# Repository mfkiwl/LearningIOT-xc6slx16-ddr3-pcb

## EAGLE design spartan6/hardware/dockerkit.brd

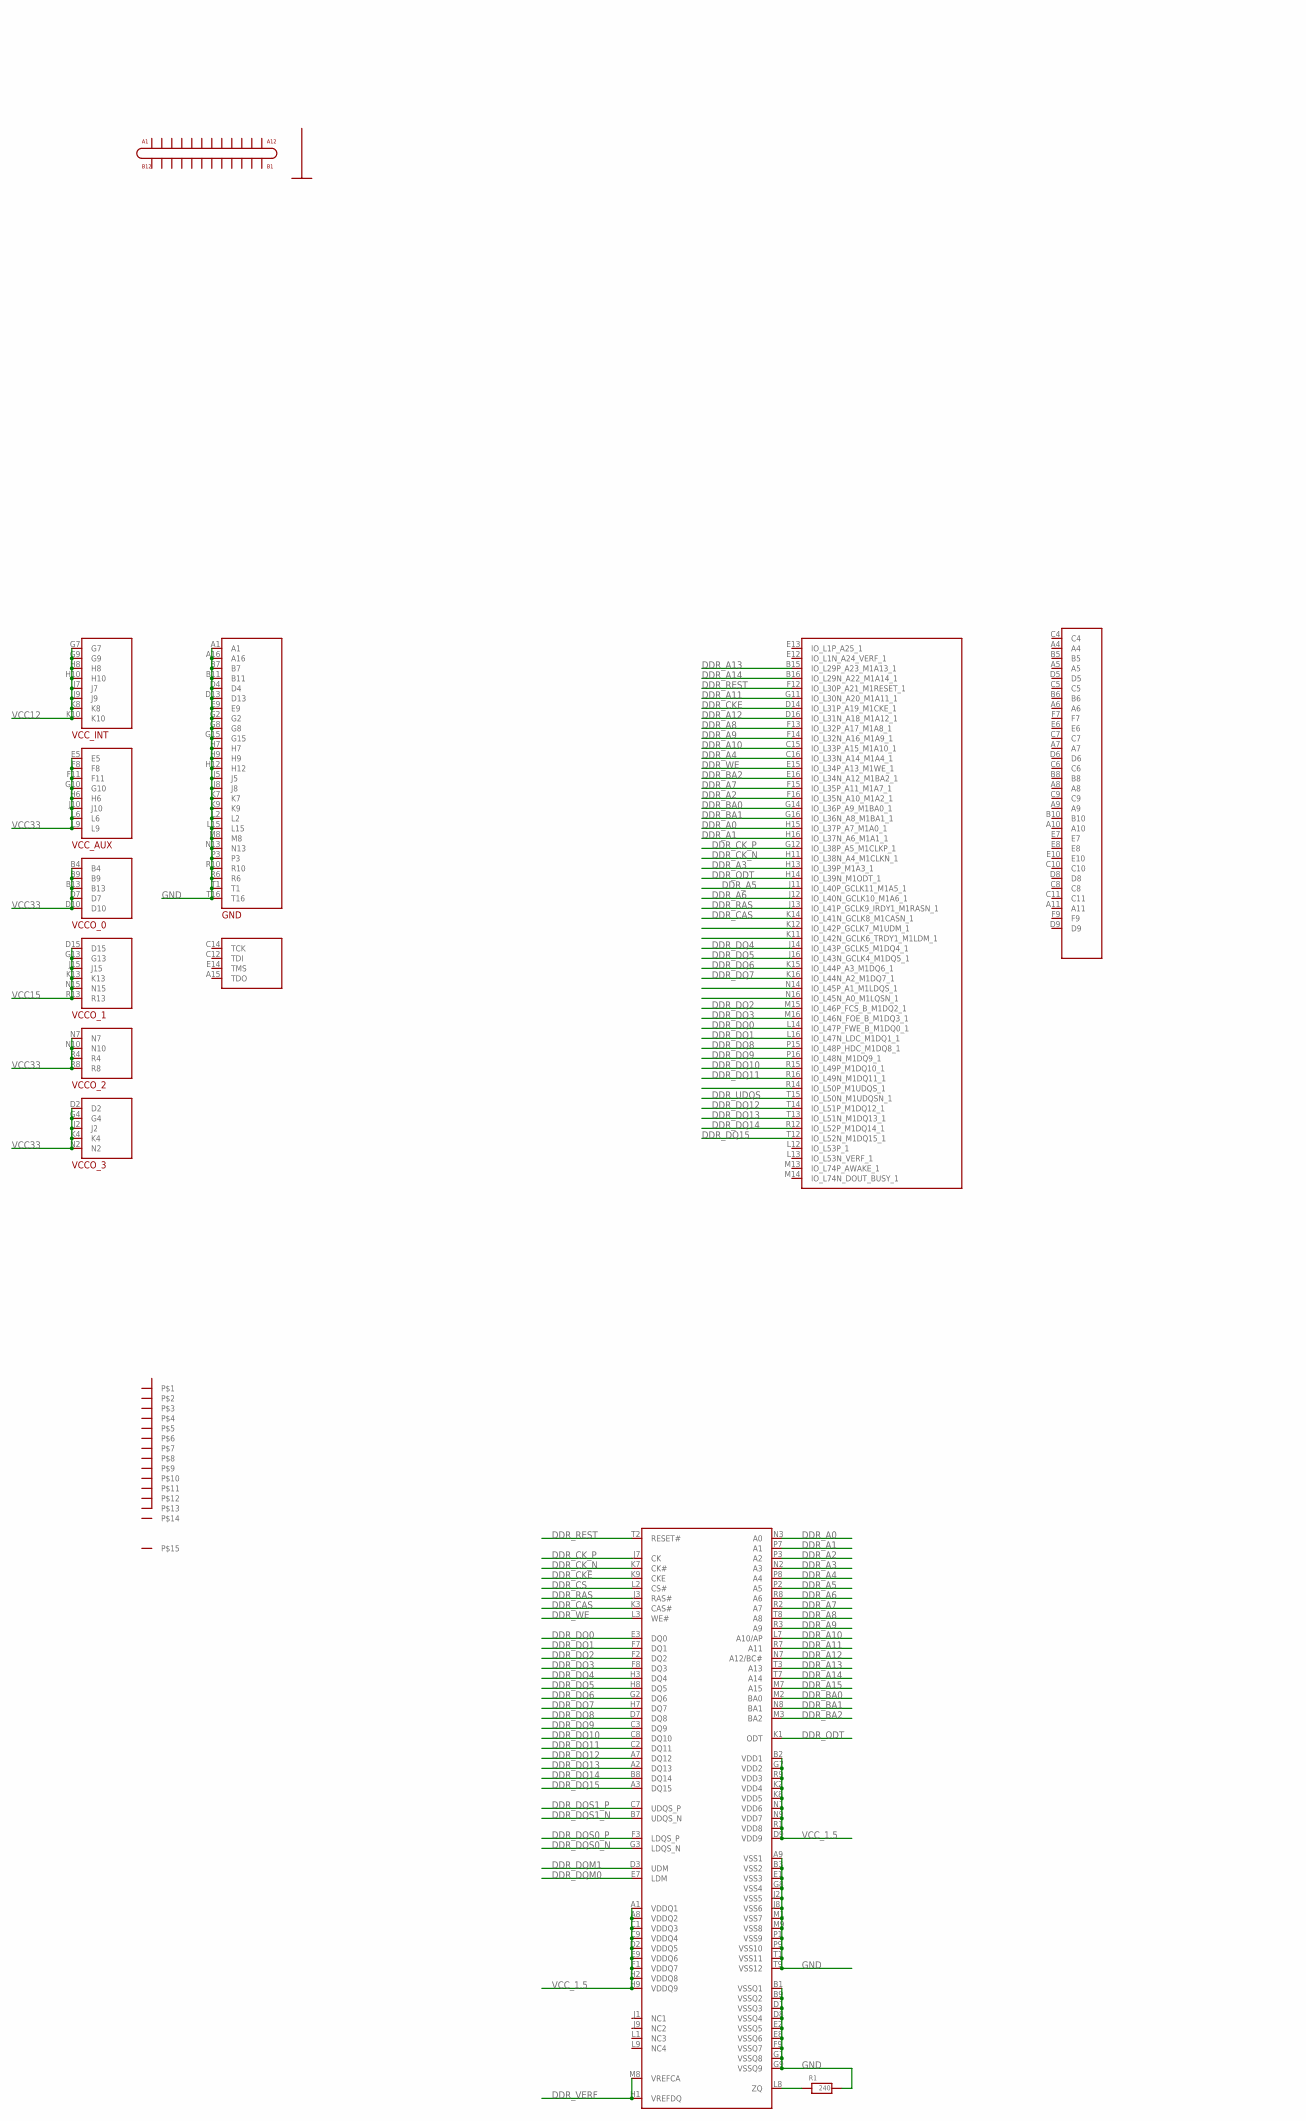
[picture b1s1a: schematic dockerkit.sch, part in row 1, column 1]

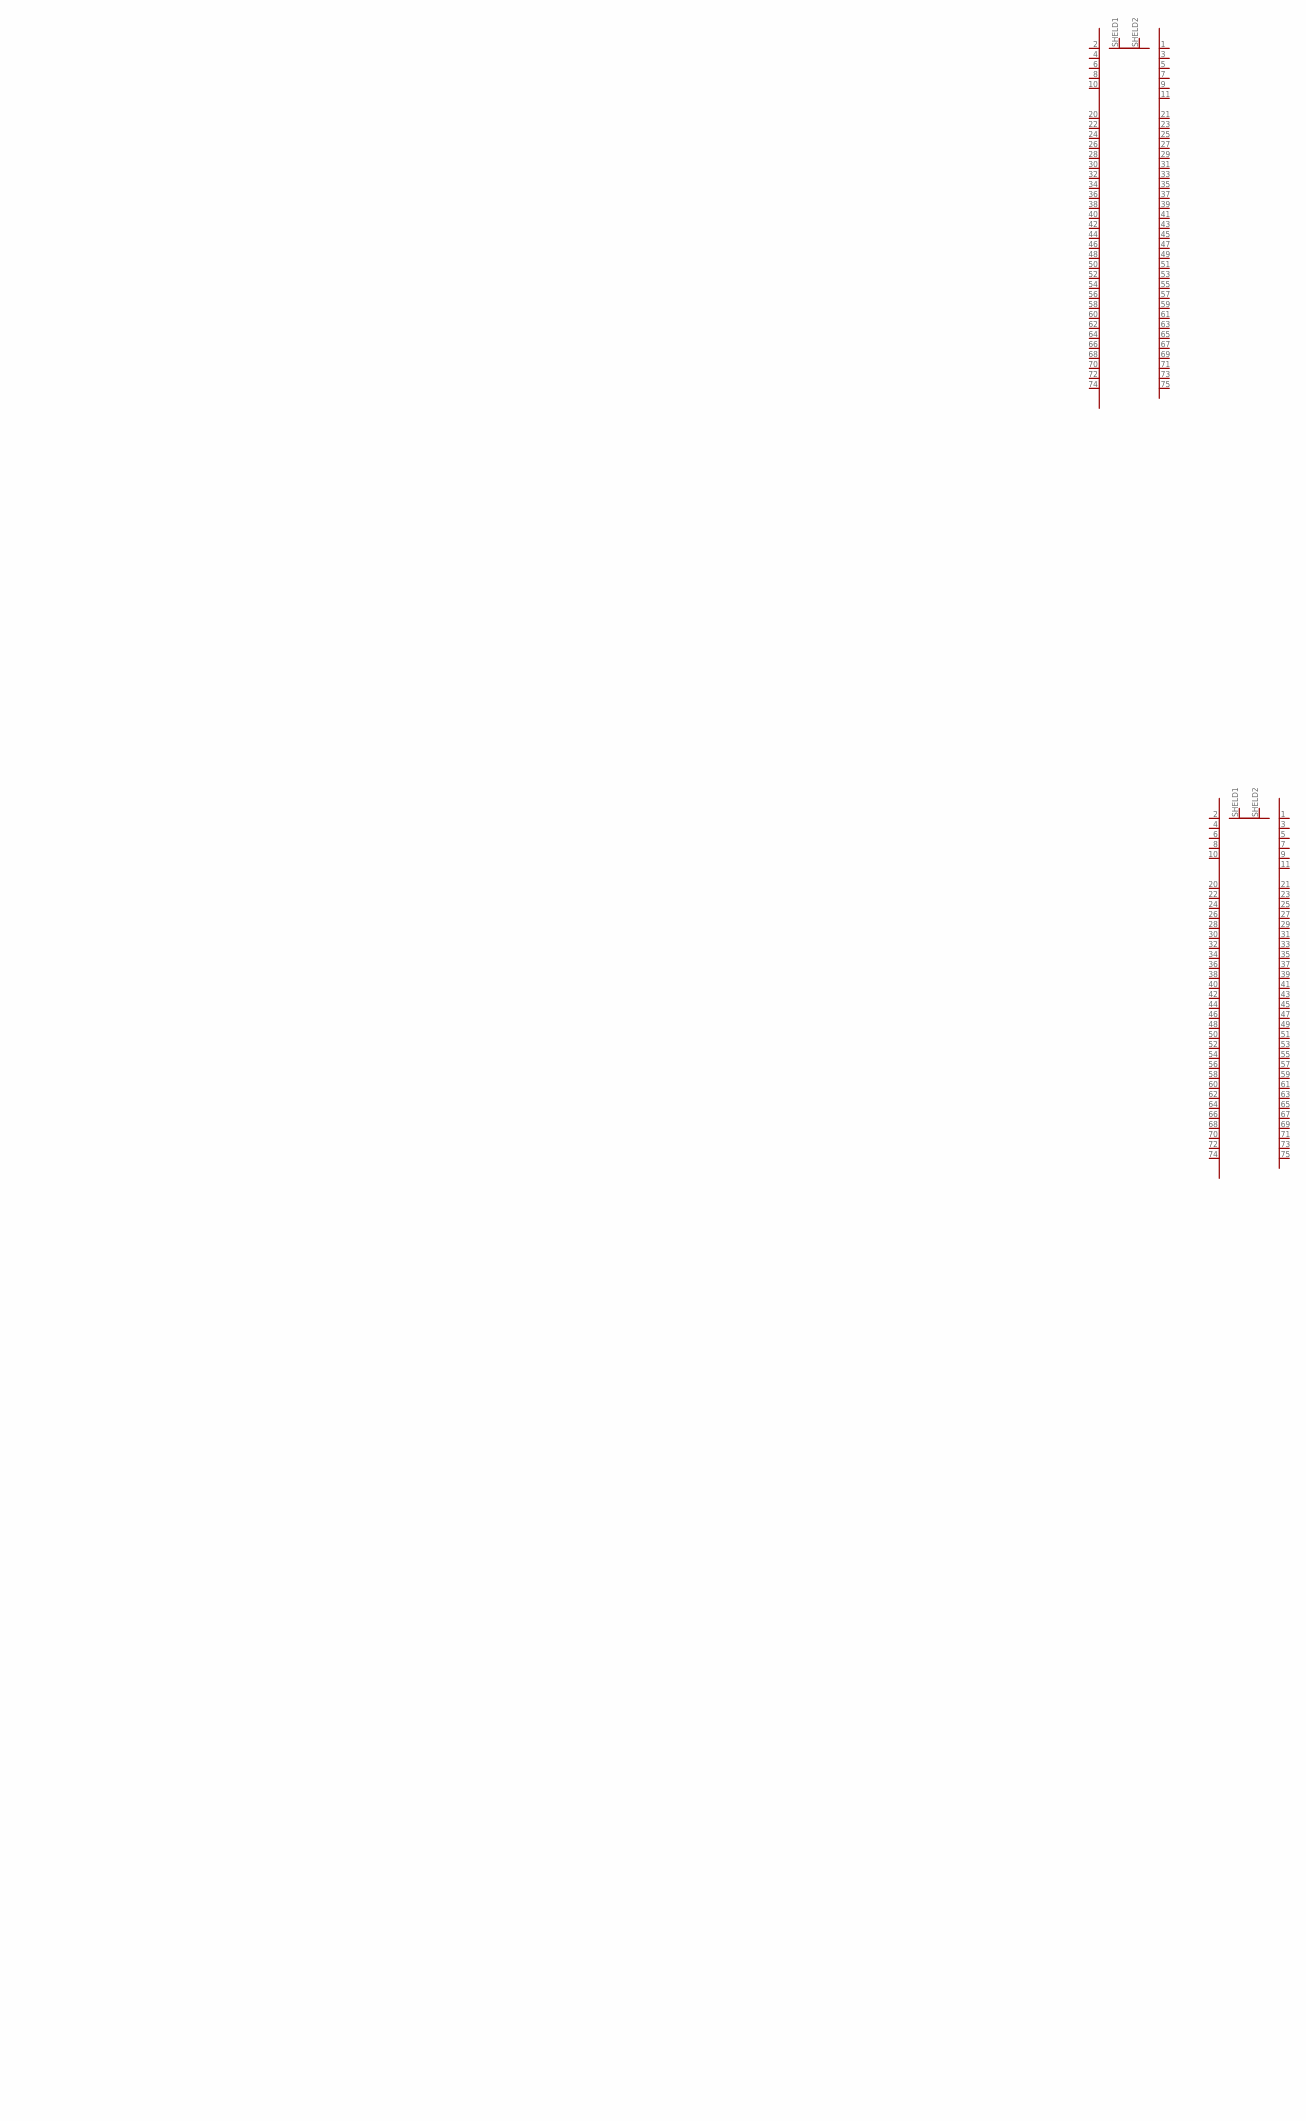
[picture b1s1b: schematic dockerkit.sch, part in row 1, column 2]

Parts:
R1: 240; R0402
U$1, U$3: B_KEY; NGFF_SOCKET
U$2: DDR3; FBGA96
U$4: XC6SLX16; FTG256
U$5: USB3.1; USB3.1_24PIN
U$8: GIGABYTE_14P; GIGABYTE_RJ45

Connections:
DDR_A0: U$2.N3 (A0), U$4.H15 (IO_L37P_A7_M1A0_1)
DDR_A1: U$2.P7 (A1), U$4.H16 (IO_L37N_A6_M1A1_1)
DDR_A2: U$2.P3 (A2), U$4.F16 (IO_L35N_A10_M1A2_1)
DDR_A3: U$2.N2 (A3), U$4.H13 (IO_L39P_M1A3_1)
DDR_A4: U$2.P8 (A4), U$4.C16 (IO_L33N_A14_M1A4_1)
DDR_A5: U$2.P2 (A5), U$4.J11 (IO_L40P_GCLK11_M1A5_1)
DDR_A6: U$2.R8 (A6), U$4.J12 (IO_L40N_GCLK10_M1A6_1)
DDR_A7: U$2.R2 (A7), U$4.F15 (IO_L35P_A11_M1A7_1)
DDR_A8: U$2.T8 (A8), U$4.F13 (IO_L32P_A17_M1A8_1)
DDR_A9: U$2.R3 (A9), U$4.F14 (IO_L32N_A16_M1A9_1)
DDR_A10: U$2.L7 (A10/AP), U$4.C15 (IO_L33P_A15_M1A10_1)
DDR_A11: U$2.R7 (A11), U$4.G11 (IO_L30N_A20_M1A11_1)
DDR_A12: U$2.N7 (A12/BC#), U$4.D16 (IO_L31N_A18_M1A12_1)
DDR_A13: U$2.T3 (A13), U$4.B15 (IO_L29P_A23_M1A13_1)
DDR_A14: U$2.T7 (A14), U$4.B16 (IO_L29N_A22_M1A14_1)
DDR_A15: U$2.M7 (A15)
DDR_BA0: U$2.M2 (BA0), U$4.G14 (IO_L36P_A9_M1BA0_1)
DDR_BA1: U$2.N8 (BA1), U$4.G16 (IO_L36N_A8_M1BA1_1)
DDR_BA2: U$2.M3 (BA2), U$4.E16 (IO_L34N_A12_M1BA2_1)
DDR_CAS: U$2.K3 (CAS#), U$4.K14 (IO_L41N_GCLK8_M1CASN_1)
DDR_CKE: U$2.K9 (CKE), U$4.D14 (IO_L31P_A19_M1CKE_1)
DDR_CK_N: U$2.K7 (CK#), U$4.H11 (IO_L38N_A4_M1CLKN_1)
DDR_CK_P: U$2.J7 (CK), U$4.G12 (IO_L38P_A5_M1CLKP_1)
DDR_CS: U$2.L2 (CS#)
DDR_DQ0: U$2.E3 (DQ0), U$4.L14 (IO_L47P_FWE_B_M1DQ0_1)
DDR_DQ1: U$2.F7 (DQ1), U$4.L16 (IO_L47N_LDC_M1DQ1_1)
DDR_DQ2: U$2.F2 (DQ2), U$4.M15 (IO_L46P_FCS_B_M1DQ2_1)
DDR_DQ3: U$2.F8 (DQ3), U$4.M16 (IO_L46N_FOE_B_M1DQ3_1)
DDR_DQ4: U$2.H3 (DQ4), U$4.J14 (IO_L43P_GCLK5_M1DQ4_1)
DDR_DQ5: U$2.H8 (DQ5), U$4.J16 (IO_L43N_GCLK4_M1DQ5_1)
DDR_DQ6: U$2.G2 (DQ6), U$4.K15 (IO_L44P_A3_M1DQ6_1)
DDR_DQ7: U$2.H7 (DQ7), U$4.K16 (IO_L44N_A2_M1DQ7_1)
DDR_DQ8: U$2.D7 (DQ8), U$4.P15 (IO_L48P_HDC_M1DQ8_1)
DDR_DQ9: U$2.C3 (DQ9), U$4.P16 (IO_L48N_M1DQ9_1)
DDR_DQ10: U$2.C8 (DQ10), U$4.R15 (IO_L49P_M1DQ10_1)
DDR_DQ11: U$2.C2 (DQ11), U$4.R16 (IO_L49N_M1DQ11_1)
DDR_DQ12: U$2.A7 (DQ12), U$4.T14 (IO_L51P_M1DQ12_1)
DDR_DQ13: U$2.A2 (DQ13), U$4.T13 (IO_L51N_M1DQ13_1)
DDR_DQ14: U$2.B8 (DQ14), U$4.R12 (IO_L52P_M1DQ14_1)
DDR_DQ15: U$2.A3 (DQ15), U$4.T12 (IO_L52N_M1DQ15_1)
DDR_DQM0: U$2.E7 (LDM)
DDR_DQM1: U$2.D3 (UDM)
DDR_DQS0_N: U$2.G3 (LDQS_N)
DDR_DQS0_P: U$2.F3 (LDQS_P)
DDR_DQS1_N: U$2.B7 (UDQS_N)
DDR_DQS1_P: U$2.C7 (UDQS_P)
DDR_ODT: U$2.K1 (ODT), U$4.H14 (IO_L39N_M1ODT_1)
DDR_RAS: U$2.J3 (RAS#), U$4.J13 (IO_L41P_GCLK9_IRDY1_M1RASN_1)
DDR_REST: U$2.T2 (RESET#), U$4.F12 (IO_L30P_A21_M1RESET_1)
DDR_UDQS: U$4.T15 (IO_L50N_M1UDQSN_1)
DDR_VERF: U$2.H1 (VREFDQ), U$2.M8 (VREFCA)
DDR_WE: U$2.L3 (WE#), U$4.E15 (IO_L34P_A13_M1WE_1)
GND: R1.- (2), U$2.A9 (VSS1), U$2.B1 (VSSQ1), U$2.B3 (VSS2), U$2.B9 (VSSQ2), U$2.D1 (VSSQ3), U$2.D8 (VSSQ4), U$2.E1 (VSS3), U$2.E2 (VSSQ5), U$2.E8 (VSSQ6), U$2.F9 (VSSQ7), U$2.G1 (VSSQ8), U$2.G8 (VSS4), U$2.G9 (VSSQ9), U$2.J2 (VSS5), U$2.J8 (VSS6), U$2.M1 (VSS7), U$2.M9 (VSS8), U$2.P1 (VSS9), U$2.P9 (VSS10), U$2.T1 (VSS11), U$2.T9 (VSS12), U$4.A1, U$4.A16, U$4.B7, U$4.B11, U$4.D4, U$4.D13, U$4.E9, U$4.G2, U$4.G8, U$4.G15, U$4.H7, U$4.H9, U$4.H12, U$4.J5, U$4.J8, U$4.K7, U$4.K9, U$4.L2, U$4.L15, U$4.M8, U$4.N13, U$4.P3, U$4.R6, U$4.R10, U$4.T1, U$4.T16
unnamed: R1.+ (1), U$2.L8 (ZQ)
VCC12: U$4.G7, U$4.G9, U$4.H8, U$4.H10, U$4.J7, U$4.J9, U$4.K8, U$4.K10
VCC15: U$4.D15, U$4.G13, U$4.J15, U$4.K13, U$4.N15, U$4.R13
VCC33: U$4.B4, U$4.B9, U$4.B13, U$4.D2, U$4.D7, U$4.D10, U$4.E5, U$4.F8, U$4.F11, U$4.G4, U$4.G10, U$4.H6, U$4.J2, U$4.J10, U$4.K4, U$4.L6, U$4.L9, U$4.N2, U$4.N7, U$4.N10, U$4.R4, U$4.R8
VCC_1.5: U$2.A1 (VDDQ1), U$2.A8 (VDDQ2), U$2.B2 (VDD1), U$2.C1 (VDDQ3), U$2.C9 (VDDQ4), U$2.D2 (VDDQ5), U$2.D9 (VDD9), U$2.E9 (VDDQ6), U$2.F1 (VDDQ7), U$2.G7 (VDD2), U$2.H2 (VDDQ8), U$2.H9 (VDDQ9), U$2.K2 (VDD4), U$2.K8 (VDD5), U$2.N1 (VDD6), U$2.N9 (VDD7), U$2.R1 (VDD8), U$2.R9 (VDD3)

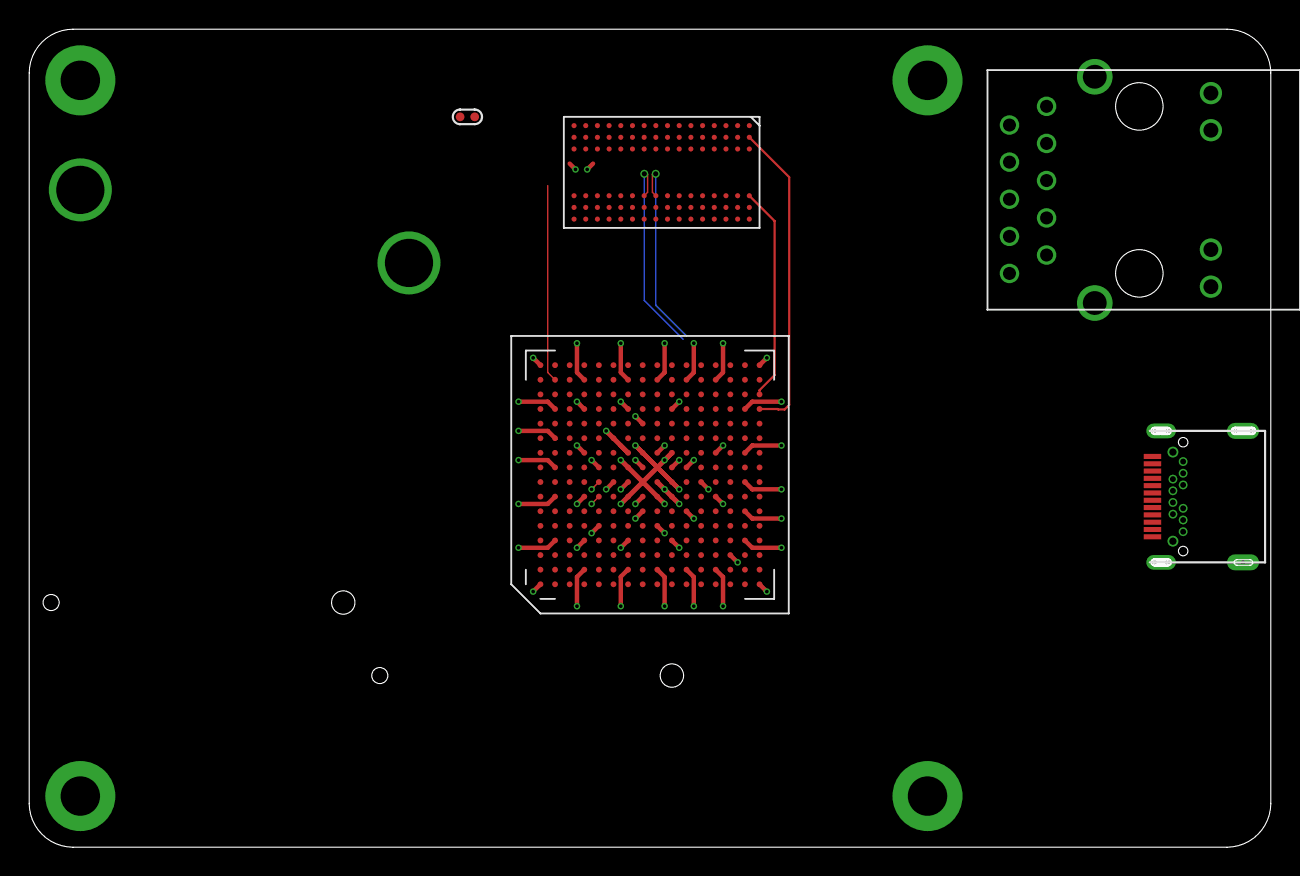
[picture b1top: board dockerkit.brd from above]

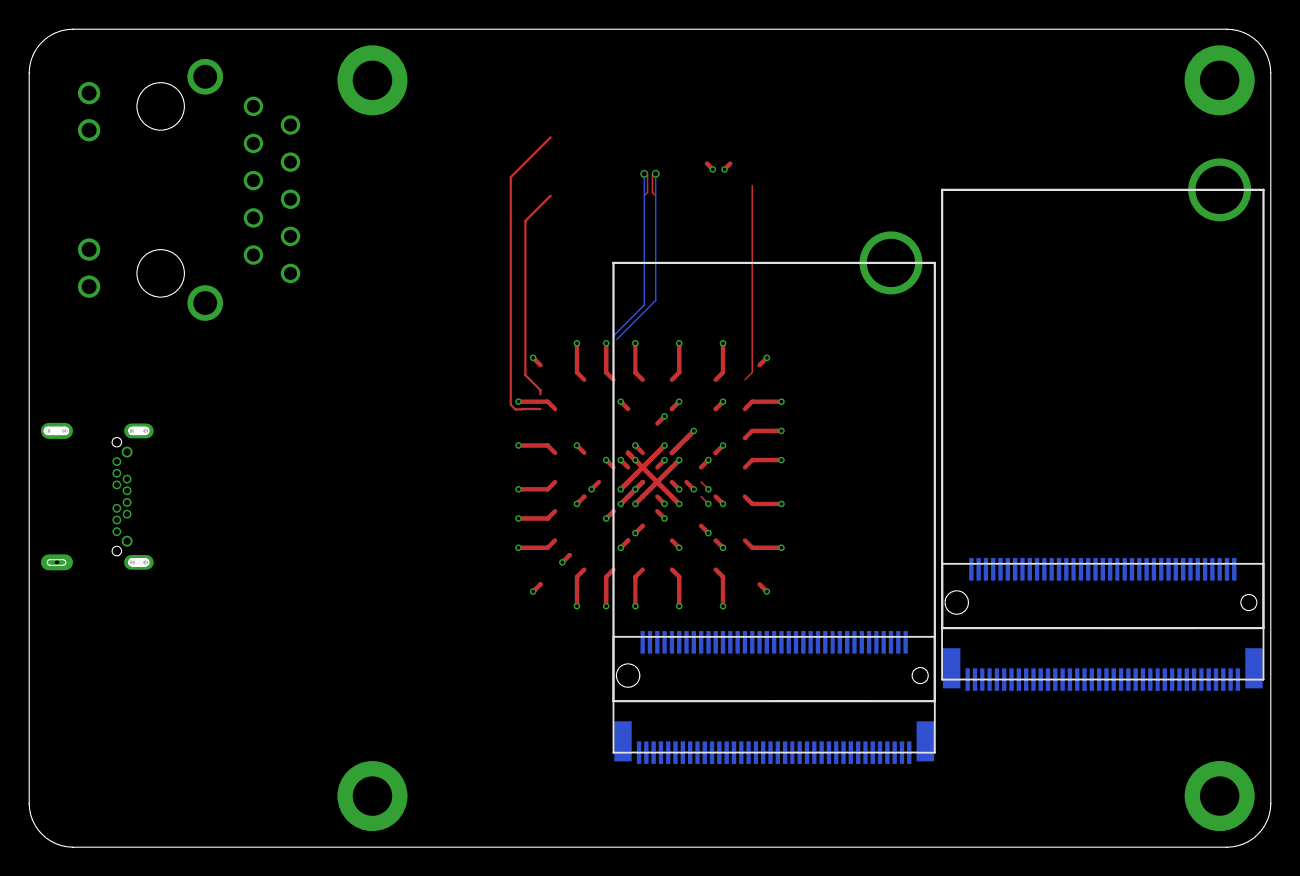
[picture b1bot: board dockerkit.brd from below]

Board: 4 copper layers, 85.0 x 56.0 mm, 7 parts (2 on the bottom side), 49 nets.

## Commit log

2019-11-14 添加f401代码
2019-11-14 添加stm32和stm8源码
2019-11-15 添加stm8源码
2019-11-17 调整目录结构
2019-11-18 添加f401cc开发板
2019-11-18 添加build目录
2019-11-18 顺利编译通过
2019-11-18 调整flash分区和引脚定义
2019-11-19 编译成功
2019-11-19 外部晶振未能启用
2019-11-19 编译成功，起振成功
2019-11-19 使用内部晶振
2019-11-22 添加ST7735S屏控制代码
2019-11-23 调整LCD驱动排版
2019-11-23 删除不必要的文件，调整结构
2019-11-23 成功编译
2019-11-27 修改GPIO定义
2019-11-27 16M外部晶振正常起振
    32768晶振未能正常起振
2019-11-28 通过编译
2020-04-01 添加显示屏代码
2020-04-01 添加FPGA部分内容
2020-04-01 添加约束
2020-04-06 开始设计FPGA转发器
2020-04-07 提交变更
2020-04-10 模块化拆分
2020-04-15 修改FPGA设计内容
2020-04-18 修改配置
2020-04-21 调整外设时钟
2020-04-29 调整时钟频率
    调整时钟，将低速时钟设置成3.3M，16.6M，33.3M
2020-04-29 调整时钟引脚设置
2020-04-29 添加时钟
2020-04-29 调整高频时钟，已正确输出
2020-05-03 在交换机代码中添加时钟代码
2020-05-03 添加IO文件实现内容
2020-05-24 添加FPGA引脚定义
2020-05-26 Update core_spartan6.md
    添加USB定义
2020-05-26 将扩展板1定义提取为独立文件
2020-06-04 添加扩展板
2020-06-05 修改扩展板引脚
2020-06-27 调整电路
